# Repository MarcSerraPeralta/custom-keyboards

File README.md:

# custom-keyboards

Documentation for designing and building custom keyboards.

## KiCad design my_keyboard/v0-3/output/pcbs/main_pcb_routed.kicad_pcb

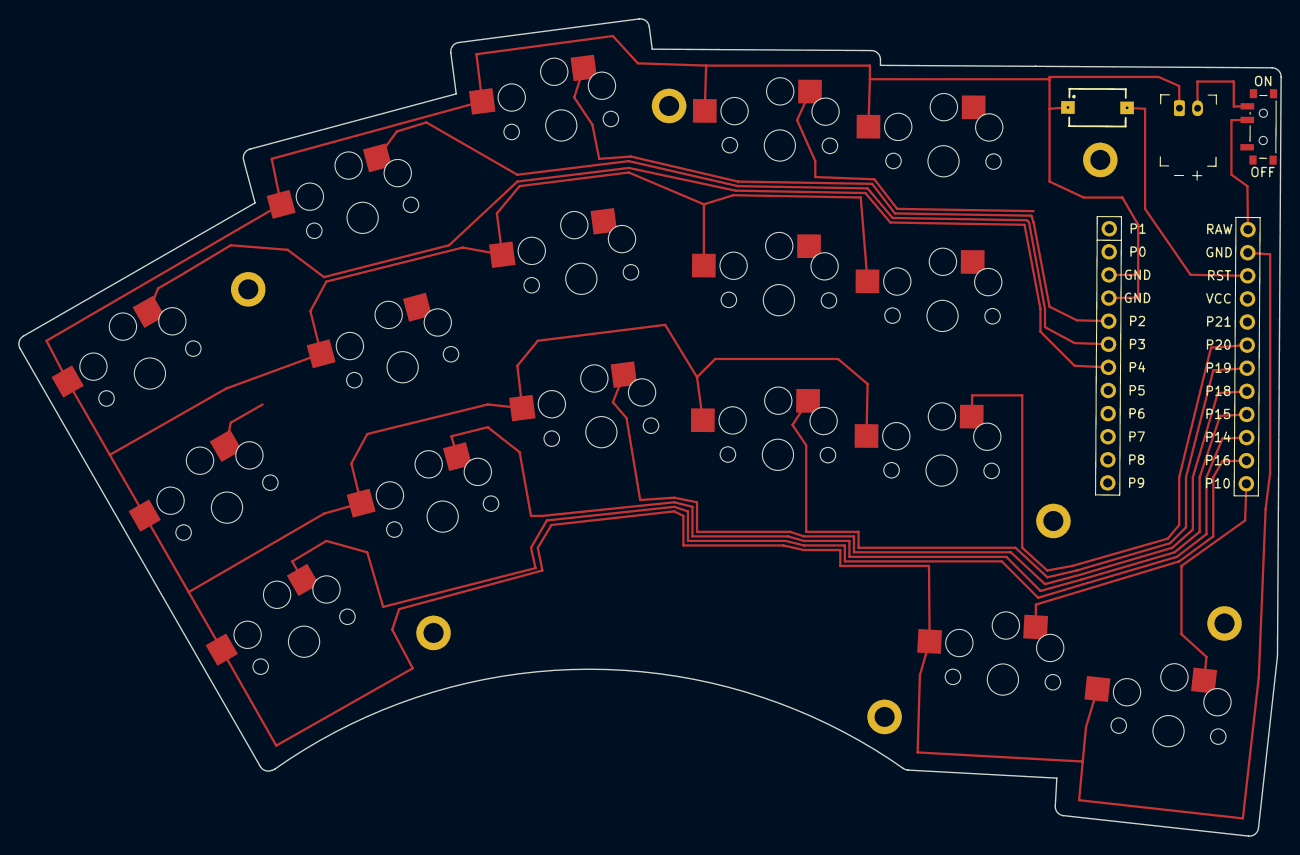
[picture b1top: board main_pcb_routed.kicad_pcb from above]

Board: 2 copper layers, 138.7 x 89.8 mm, 28 parts (0 on the bottom side), 21 nets.

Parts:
H1, H2, H3, H4, H5, H6, H7: mounting_hole_plated
JST1: battery_connector_jst_ph_2
MCU1: mcu_supermini_nrf52840
PWR1: power_switch_smd_side
S1, S2, S3, S4, S5, S6, S7, S8, S9, S10, S11, S12, S13, S14, S15, S16, S17: PG1350
S18: 434121025816

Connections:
GND: JST1.1, MCU1.2, MCU1.21, MCU1.22, S1.2, S2.2, S3.2, S4.2, S5.2, S6.2, S7.2, S8.2, S9.2, S10.2, S11.2, S12.2, S13.2, S14.2, S15.2, S16.2, S17.2, S18.1
P0: MCU1.23, S12.1
P1: MCU1.24, S15.1
P2: MCU1.20, S9.1
P3: MCU1.19, S6.1
P4: MCU1.18, S3.1
P5: MCU1.17, S14.1
P6: MCU1.16, S11.1
P7: MCU1.15, S8.1
P8: MCU1.14, S5.1
P9: MCU1.13, S2.1
P10: MCU1.12, S17.1
P14: MCU1.10, S1.1
P15: MCU1.9, S4.1
P16: MCU1.11, S16.1
P18: MCU1.8, S7.1
P19: MCU1.7, S10.1
P20: MCU1.6, S13.1
PWR_SW: JST1.2, PWR1.1, PWR1.3
RAW: MCU1.1, PWR1.2
RST: MCU1.3, S18.2

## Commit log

2024-10-09 Add current information
2024-11-06 Update information and layouts
2024-11-10 Update docs
2024-12-28 Add version 0.3 of my keyboard
2025-01-04 reversible PCBs
2025-01-06 Add complete v0.3
2025-01-25 Add docs and v0-3
2025-01-26 Move elements in PCB so that routing is easier
2025-01-26 Solve bug in P0 and P1 nets
2026-05-24 Rename force-travel diagrams
2026-05-24 Add EXAMPLES.md
2026-05-24 Move scripts to utils/ directory
2026-05-25 Improve documentation and switch to Markdown
2026-05-25 Differentiate hardware and software design
2026-05-25 Add more documentation
2026-05-28 Add HARDWARE.md
